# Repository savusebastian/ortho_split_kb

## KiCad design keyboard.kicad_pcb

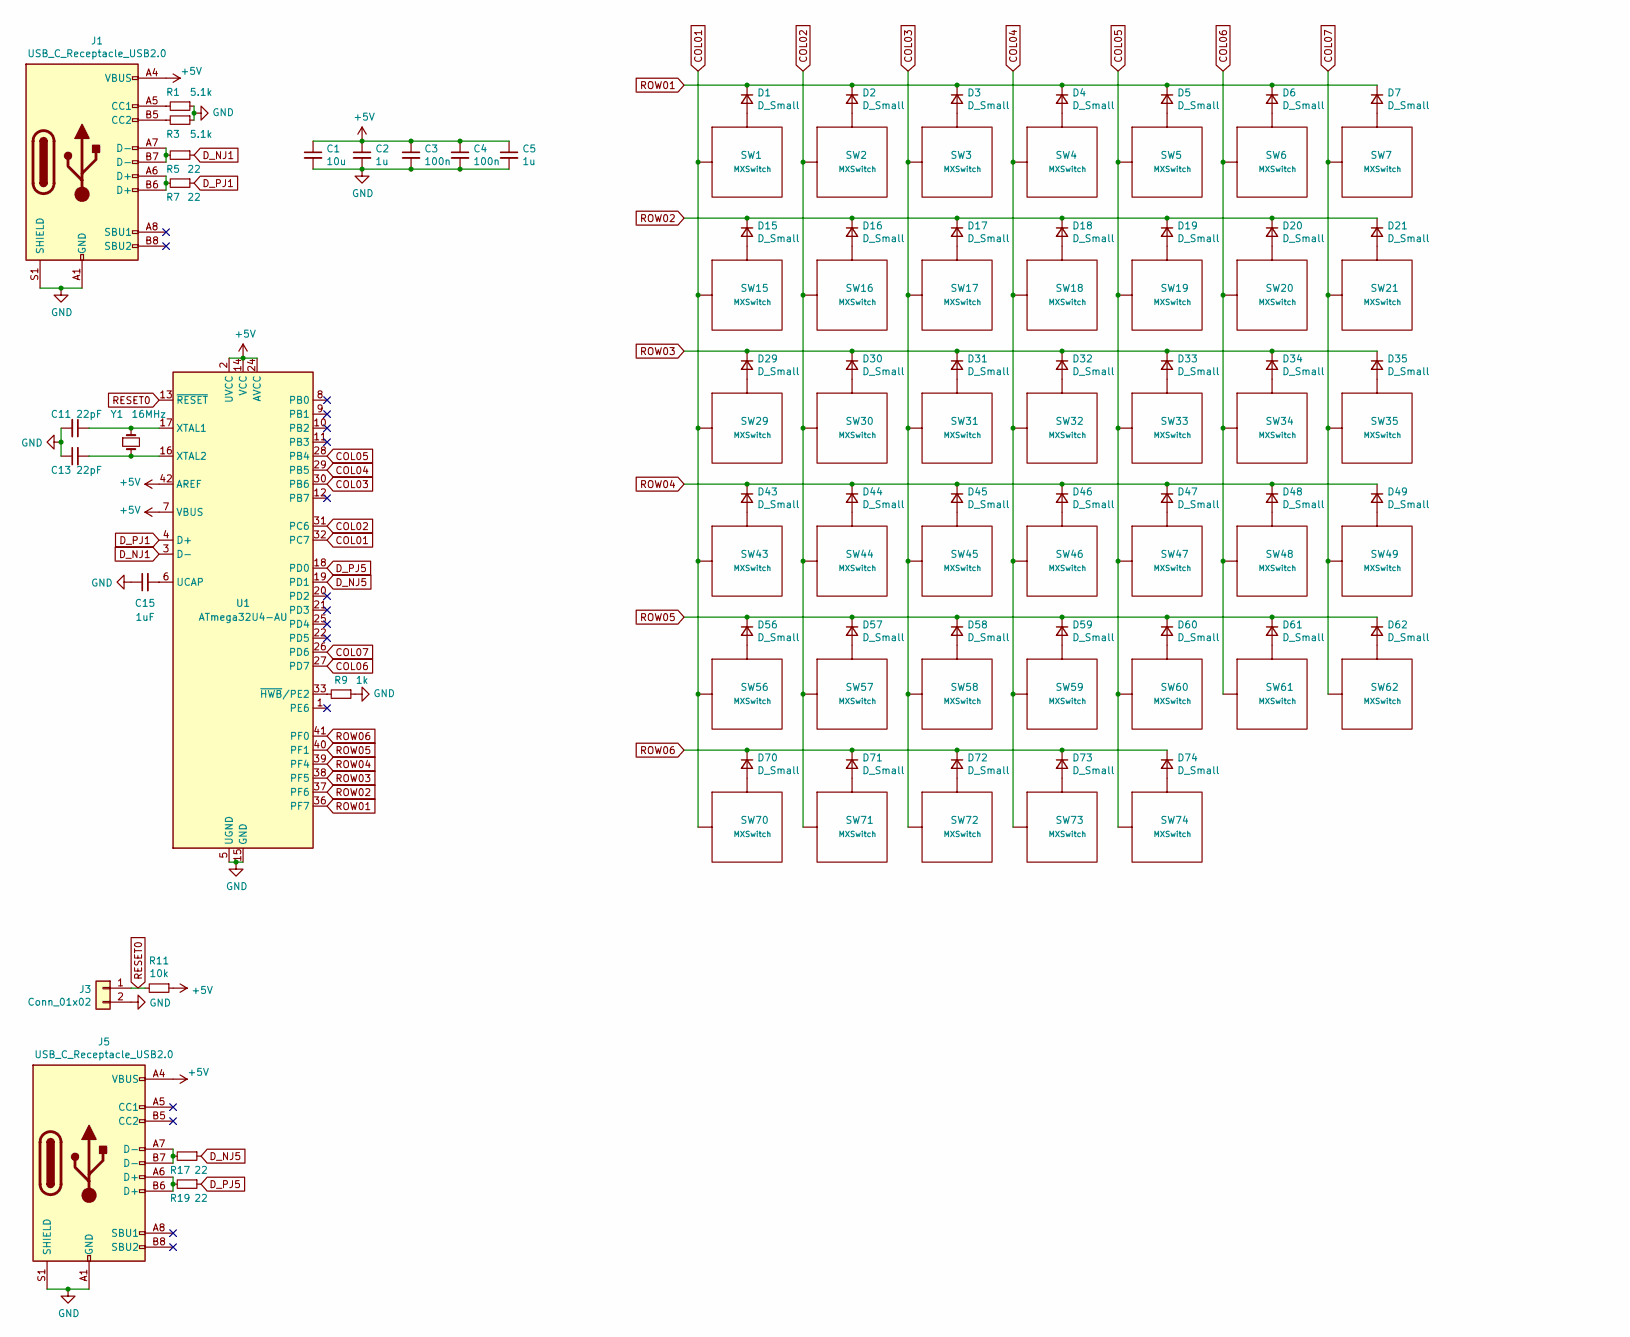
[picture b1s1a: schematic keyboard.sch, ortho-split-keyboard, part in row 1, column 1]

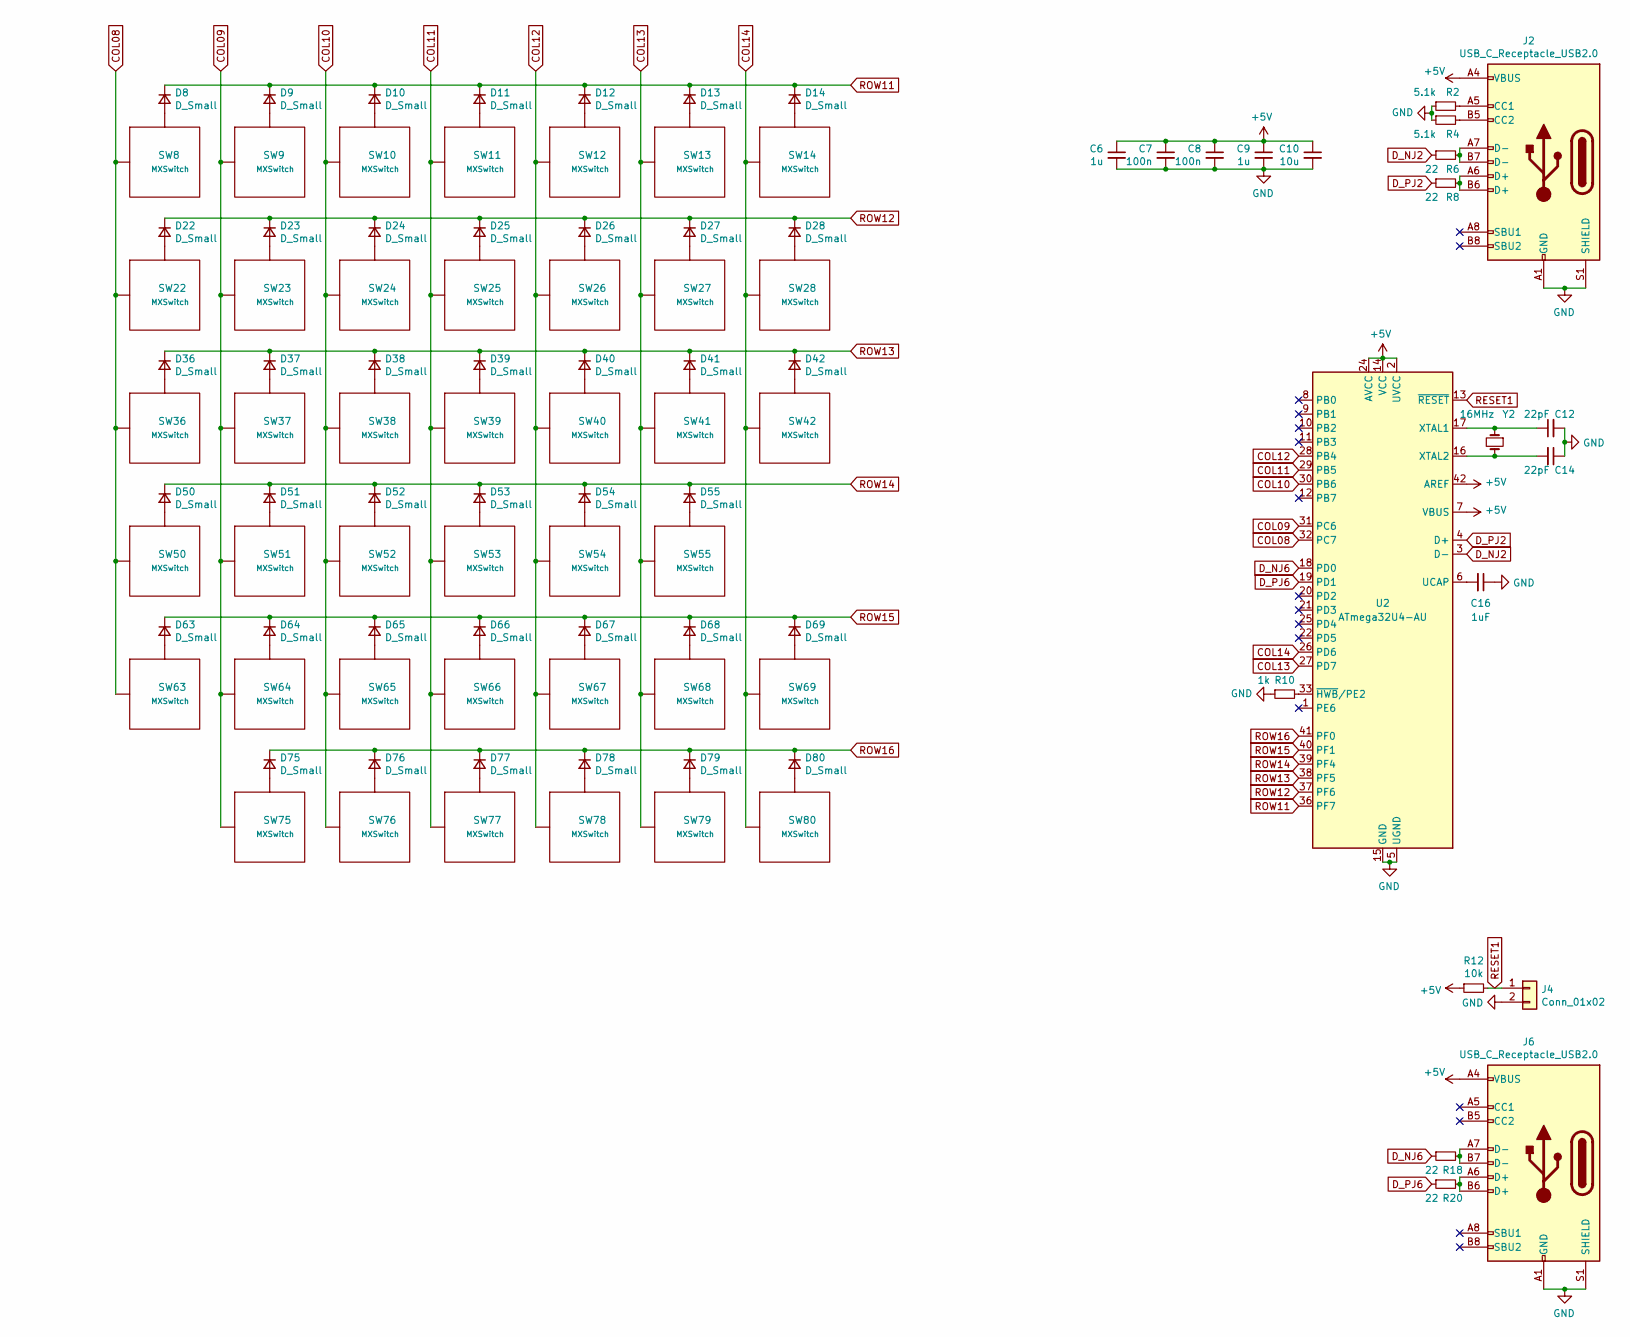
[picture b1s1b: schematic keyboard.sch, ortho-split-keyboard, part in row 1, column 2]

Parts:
C1, C10: 10u; C_0201_0603Metric; LCSC C1691
C2, C5, C6, C9: 1u; C_0201_0603Metric; LCSC C29936
C3, C4, C7, C8: 100n; C_0201_0603Metric; LCSC C1591
C11, C12, C13, C14: 22pF; C_0201_0603Metric; LCSC C1653
C15, C16: 1uF; C_0201_0603Metric; LCSC C29936
D1, D2, D3, D4, D5, D6, D7, D8, D9, D10, D11, D12, D13, D14, D15, D16, D17, D18, D19, D20, D21, D22, D23, D24, D25, D26, D27, D28, D29, D30, D31, D32, D33, D34, D35, D36, D37, D38, D39, D40, D41, D42, D43, D44, D45, D46, D47, D48, D49, D50, D51, D52, D53, D54, D55, D56, D57, D58, D59, D60, D61, D62, D63, D64, D65, D66, D67, D68, D69, D70, D71, D72, D73, D74, D75, D76, D77, D78, D79, D80: D_Small; D_0603_1608Metric; LCSC C316054
J1, J2, J5, J6: USB_C_Receptacle_USB2.0; USB_C_Receptacle_Amphenol_12401548E4-2A
J3, J4: Conn_01x02; PinHeader_1x02_P2.54mm_Vertical
R1, R2, R3, R4: 5.1k; R_0603_1608Metric; LCSC C14677
R5, R6, R7, R8, R17, R18, R19, R20: 22; R_0603_1608Metric; LCSC C108405
R9, R10: 1k; R_0603_1608Metric; LCSC C14676
R11, R12: 10k; R_0603_1608Metric; LCSC C98220
SW1, SW2, SW3, SW4, SW5, SW6, SW7, SW8, SW9, SW10, SW11, SW12, SW13, SW14, SW15, SW16, SW17, SW18, SW19, SW20, SW21, SW22, SW23, SW24, SW25, SW26, SW27, SW28, SW29, SW30, SW31, SW32, SW33, SW34, SW35, SW36, SW37, SW38, SW39, SW40, SW41, SW42, SW43, SW44, SW45, SW46, SW47, SW48, SW49, SW50, SW51, SW52, SW53, SW54, SW56, SW57, SW58, SW59, SW60, SW61, SW62, SW63, SW64, SW65, SW66, SW67, SW68, SW69, SW70, SW71, SW72, SW73, SW75, SW76, SW77, SW78, SW79, SW80: MXSwitch; SW_Cherry_MX_1.00u_PCB
SW55, SW74: MXSwitch; SW_Cherry_MX_2.00u_PCB
U1, U2: ATmega32U4-AU; TQFP-44_10x10mm_P0.8mm; LCSC C44854
Y1, Y2: 16MHz; Crystal_SMD_5032-2Pin_5.0x3.2mm; LCSC C568455

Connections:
+5V: C1.1, C2.1, C3.1, C4.1, C5.1, C6.1, C7.1, C8.1, C9.1, C10.1, J1.A4 (VBUS), J1.A9 (VBUS), J1.B4 (VBUS), J1.B9 (VBUS), J2.A4 (VBUS), J2.A9 (VBUS), J2.B4 (VBUS), J2.B9 (VBUS), J5.A4 (VBUS), J5.A9 (VBUS), J5.B4 (VBUS), J5.B9 (VBUS), J6.A4 (VBUS), J6.A9 (VBUS), J6.B4 (VBUS), J6.B9 (VBUS), R11.1, R12.1, U1.2 (UVCC), U1.7 (VBUS), U1.14 (VCC), U1.24 (AVCC), U1.34 (VCC), U1.42 (AREF), U1.44 (AVCC), U2.2 (UVCC), U2.7 (VBUS), U2.14 (VCC), U2.24 (AVCC), U2.34 (VCC), U2.42 (AREF), U2.44 (AVCC)
COL01: SW1.1 (Col), SW15.1 (Col), SW29.1 (Col), SW43.1 (Col), SW56.1 (Col), SW70.1 (Col), U1.32 (PC7)
COL02: SW2.1 (Col), SW16.1 (Col), SW30.1 (Col), SW44.1 (Col), SW57.1 (Col), SW71.1 (Col), U1.31 (PC6)
COL03: SW3.1 (Col), SW17.1 (Col), SW31.1 (Col), SW45.1 (Col), SW58.1 (Col), SW72.1 (Col), U1.30 (PB6)
COL04: SW4.1 (Col), SW18.1 (Col), SW32.1 (Col), SW46.1 (Col), SW59.1 (Col), SW73.1 (Col), U1.29 (PB5)
COL05: SW5.1 (Col), SW19.1 (Col), SW33.1 (Col), SW47.1 (Col), SW60.1 (Col), SW74.1 (Col), U1.28 (PB4)
COL06: SW6.1 (Col), SW20.1 (Col), SW34.1 (Col), SW48.1 (Col), SW61.1 (Col), U1.27 (PD7)
COL07: SW7.1 (Col), SW21.1 (Col), SW35.1 (Col), SW49.1 (Col), SW62.1 (Col), U1.26 (PD6)
COL08: SW8.1 (Col), SW22.1 (Col), SW36.1 (Col), SW50.1 (Col), SW63.1 (Col), U2.32 (PC7)
COL09: SW9.1 (Col), SW23.1 (Col), SW37.1 (Col), SW51.1 (Col), SW64.1 (Col), SW75.1 (Col), U2.31 (PC6)
COL10: SW10.1 (Col), SW24.1 (Col), SW38.1 (Col), SW52.1 (Col), SW65.1 (Col), SW76.1 (Col), U2.30 (PB6)
COL11: SW11.1 (Col), SW25.1 (Col), SW39.1 (Col), SW53.1 (Col), SW66.1 (Col), SW77.1 (Col), U2.29 (PB5)
COL12: SW12.1 (Col), SW26.1 (Col), SW40.1 (Col), SW54.1 (Col), SW67.1 (Col), SW78.1 (Col), U2.28 (PB4)
COL13: SW13.1 (Col), SW27.1 (Col), SW41.1 (Col), SW55.1 (Col), SW68.1 (Col), SW79.1 (Col), U2.27 (PD7)
COL14: SW14.1 (Col), SW28.1 (Col), SW42.1 (Col), SW69.1 (Col), SW80.1 (Col), U2.26 (PD6)
D_NJ1: R5.1, U1.3 (D-)
D_NJ2: R6.1, U2.3 (D-)
D_NJ5: R17.1, U1.19 (PD1); also elsewhere on the board
D_NJ6: R18.1, U2.18 (PD0); also elsewhere on the board
D_PJ1: R7.1, U1.4 (D+)
D_PJ2: R8.1, U2.4 (D+)
D_PJ5: R19.1, U1.18 (PD0); also elsewhere on the board
D_PJ6: R20.1, U2.19 (PD1); also elsewhere on the board
GND: C1.2, C2.2, C3.2, C4.2, C5.2, C6.2, C7.2, C8.2, C9.2, C10.2, C11.2, C12.2, C13.1, C14.1, C15.1, C16.1, J1.A1 (GND), J1.A12 (GND), J1.B1 (GND), J1.B12 (GND), J1.S1 (SHIELD), J2.A1 (GND), J2.A12 (GND), J2.B1 (GND), J2.B12 (GND), J2.S1 (SHIELD), J3.2, J4.2, J5.A1 (GND), J5.A12 (GND), J5.B1 (GND), J5.B12 (GND), J5.S1 (SHIELD), J6.A1 (GND), J6.A12 (GND), J6.B1 (GND), J6.B12 (GND), J6.S1 (SHIELD), R1.1, R2.1, R3.1, R4.1, R9.1, R10.1, U1.5 (UGND), U1.15 (GND), U1.23 (GND), U1.35 (GND), U1.43 (GND), U2.5 (UGND), U2.15 (GND), U2.23 (GND), U2.35 (GND), U2.43 (GND)
unnamed: C11.1, U1.17 (XTAL1), Y1.1
unnamed: C12.1, U2.17 (XTAL1), Y2.1
unnamed: C13.2, U1.16 (XTAL2), Y1.2
unnamed: C14.2, U2.16 (XTAL2), Y2.2
unnamed: C15.2, U1.6 (UCAP)
unnamed: C16.2, U2.6 (UCAP)
unnamed: D1.2 (A), SW1.2 (Row)
unnamed: D2.2 (A), SW2.2 (Row)
unnamed: D3.2 (A), SW3.2 (Row)
unnamed: D4.2 (A), SW4.2 (Row)
unnamed: D5.2 (A), SW5.2 (Row)
unnamed: D6.2 (A), SW6.2 (Row)
unnamed: D7.2 (A), SW7.2 (Row)
unnamed: D8.2 (A), SW8.2 (Row)
unnamed: D9.2 (A), SW9.2 (Row)
unnamed: D10.2 (A), SW10.2 (Row)
unnamed: D11.2 (A), SW11.2 (Row)
unnamed: D12.2 (A), SW12.2 (Row)
unnamed: D13.2 (A), SW13.2 (Row)
unnamed: D14.2 (A), SW14.2 (Row)
unnamed: D15.2 (A), SW15.2 (Row)
unnamed: D16.2 (A), SW16.2 (Row)
unnamed: D17.2 (A), SW17.2 (Row)
unnamed: D18.2 (A), SW18.2 (Row)
unnamed: D19.2 (A), SW19.2 (Row)
unnamed: D20.2 (A), SW20.2 (Row)
unnamed: D21.2 (A), SW21.2 (Row)
unnamed: D22.2 (A), SW22.2 (Row)
unnamed: D23.2 (A), SW23.2 (Row)
unnamed: D24.2 (A), SW24.2 (Row)
unnamed: D25.2 (A), SW25.2 (Row)
unnamed: D26.2 (A), SW26.2 (Row)
unnamed: D27.2 (A), SW27.2 (Row)
unnamed: D28.2 (A), SW28.2 (Row)
unnamed: D29.2 (A), SW29.2 (Row)
unnamed: D30.2 (A), SW30.2 (Row)
unnamed: D31.2 (A), SW31.2 (Row)
unnamed: D32.2 (A), SW32.2 (Row)
unnamed: D33.2 (A), SW33.2 (Row)
unnamed: D34.2 (A), SW34.2 (Row)
unnamed: D35.2 (A), SW35.2 (Row)
unnamed: D36.2 (A), SW36.2 (Row)
unnamed: D37.2 (A), SW37.2 (Row)
unnamed: D38.2 (A), SW38.2 (Row)
unnamed: D39.2 (A), SW39.2 (Row)
unnamed: D40.2 (A), SW40.2 (Row)
unnamed: D41.2 (A), SW41.2 (Row)
unnamed: D42.2 (A), SW42.2 (Row)
unnamed: D43.2 (A), SW43.2 (Row)
unnamed: D44.2 (A), SW44.2 (Row)
unnamed: D45.2 (A), SW45.2 (Row)
unnamed: D46.2 (A), SW46.2 (Row)
unnamed: D47.2 (A), SW47.2 (Row)
unnamed: D48.2 (A), SW48.2 (Row)
unnamed: D49.2 (A), SW49.2 (Row)
unnamed: D50.2 (A), SW50.2 (Row)
unnamed: D51.2 (A), SW51.2 (Row)
unnamed: D52.2 (A), SW52.2 (Row)
unnamed: D53.2 (A), SW53.2 (Row)
unnamed: D54.2 (A), SW54.2 (Row)
unnamed: D55.2 (A), SW55.2 (Row)
unnamed: D56.2 (A), SW56.2 (Row)
unnamed: D57.2 (A), SW57.2 (Row)
unnamed: D58.2 (A), SW58.2 (Row)
unnamed: D59.2 (A), SW59.2 (Row)
unnamed: D60.2 (A), SW60.2 (Row)
unnamed: D61.2 (A), SW61.2 (Row)
unnamed: D62.2 (A), SW62.2 (Row)
unnamed: D63.2 (A), SW63.2 (Row)
unnamed: D64.2 (A), SW64.2 (Row)
unnamed: D65.2 (A), SW65.2 (Row)
unnamed: D66.2 (A), SW66.2 (Row)
unnamed: D67.2 (A), SW67.2 (Row)
unnamed: D68.2 (A), SW68.2 (Row)
unnamed: D69.2 (A), SW69.2 (Row)
unnamed: D70.2 (A), SW70.2 (Row)
unnamed: D71.2 (A), SW71.2 (Row)
unnamed: D72.2 (A), SW72.2 (Row)
unnamed: D73.2 (A), SW73.2 (Row)
unnamed: D74.2 (A), SW74.2 (Row)
unnamed: D75.2 (A), SW75.2 (Row)
unnamed: D76.2 (A), SW76.2 (Row)
unnamed: D77.2 (A), SW77.2 (Row)
unnamed: D78.2 (A), SW78.2 (Row)
unnamed: D79.2 (A), SW79.2 (Row)
unnamed: D80.2 (A), SW80.2 (Row)
unnamed: J1.A5 (CC1), R1.2
unnamed: J1.A6 (D+), J1.B6 (D+), R7.2
unnamed: J1.A7 (D-), J1.B7 (D-), R5.2
unnamed: J1.B5 (CC2), R3.2
unnamed: J2.A5 (CC1), R2.2
unnamed: J2.A6 (D+), J2.B6 (D+), R8.2
unnamed: J2.A7 (D-), J2.B7 (D-), R6.2
unnamed: J2.B5 (CC2), R4.2
unnamed 123: J5.A6 (D+), J5.B6 (D+), R19.2; also elsewhere on the board
unnamed 124: J5.A7 (D-), J5.B7 (D-), R17.2; also elsewhere on the board
unnamed 129: J6.A6 (D+), J6.B6 (D+), R20.2; also elsewhere on the board
unnamed 130: J6.A7 (D-), J6.B7 (D-), R18.2; also elsewhere on the board
unnamed: R9.2, U1.33 (~HWB~/PE2)
unnamed: R10.2, U2.33 (~HWB~/PE2)
RESET0: J3.1, R11.2, U1.13 (~RESET)
RESET1: J4.1, R12.2, U2.13 (~RESET)
ROW01: D1.1 (K), D2.1 (K), D3.1 (K), D4.1 (K), D5.1 (K), D6.1 (K), D7.1 (K), U1.36 (PF7)
ROW02: D15.1 (K), D16.1 (K), D17.1 (K), D18.1 (K), D19.1 (K), D20.1 (K), D21.1 (K), U1.37 (PF6)
ROW03: D29.1 (K), D30.1 (K), D31.1 (K), D32.1 (K), D33.1 (K), D34.1 (K), D35.1 (K), U1.38 (PF5)
ROW04: D43.1 (K), D44.1 (K), D45.1 (K), D46.1 (K), D47.1 (K), D48.1 (K), D49.1 (K), U1.39 (PF4)
ROW05: D56.1 (K), D57.1 (K), D58.1 (K), D59.1 (K), D60.1 (K), D61.1 (K), D62.1 (K), U1.40 (PF1)
ROW06: D70.1 (K), D71.1 (K), D72.1 (K), D73.1 (K), D74.1 (K), U1.41 (PF0)
ROW11: D8.1 (K), D9.1 (K), D10.1 (K), D11.1 (K), D12.1 (K), D13.1 (K), D14.1 (K), U2.36 (PF7)
ROW12: D22.1 (K), D23.1 (K), D24.1 (K), D25.1 (K), D26.1 (K), D27.1 (K), D28.1 (K), U2.37 (PF6)
ROW13: D36.1 (K), D37.1 (K), D38.1 (K), D39.1 (K), D40.1 (K), D41.1 (K), D42.1 (K), U2.38 (PF5)
ROW14: D50.1 (K), D51.1 (K), D52.1 (K), D53.1 (K), D54.1 (K), D55.1 (K), U2.39 (PF4)
ROW15: D63.1 (K), D64.1 (K), D65.1 (K), D66.1 (K), D67.1 (K), D68.1 (K), D69.1 (K), U2.40 (PF1)
ROW16: D75.1 (K), D76.1 (K), D77.1 (K), D78.1 (K), D79.1 (K), D80.1 (K), U2.41 (PF0)

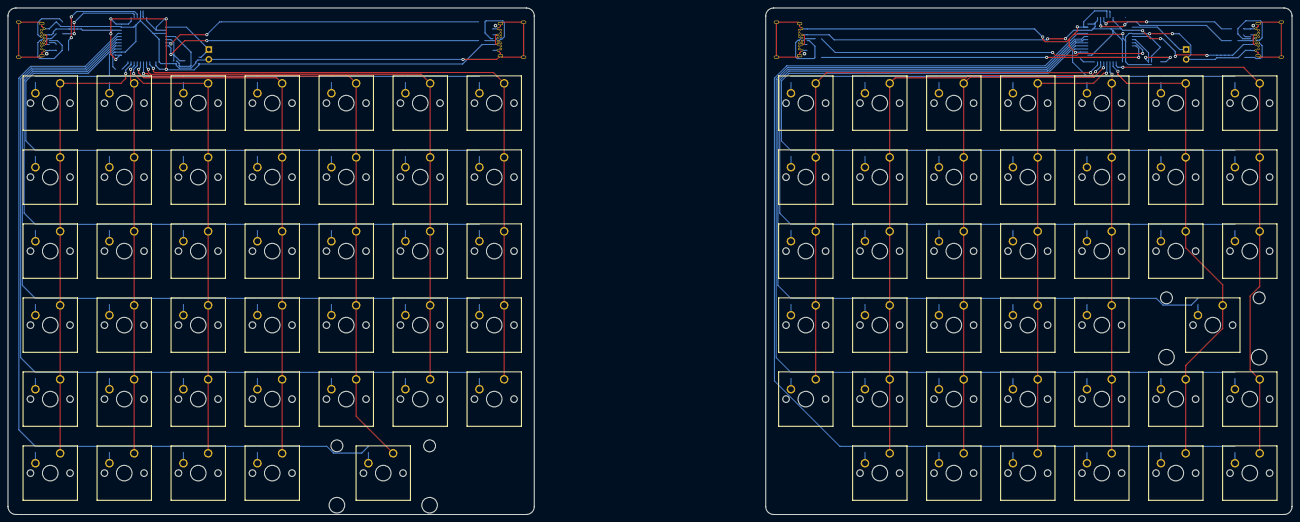
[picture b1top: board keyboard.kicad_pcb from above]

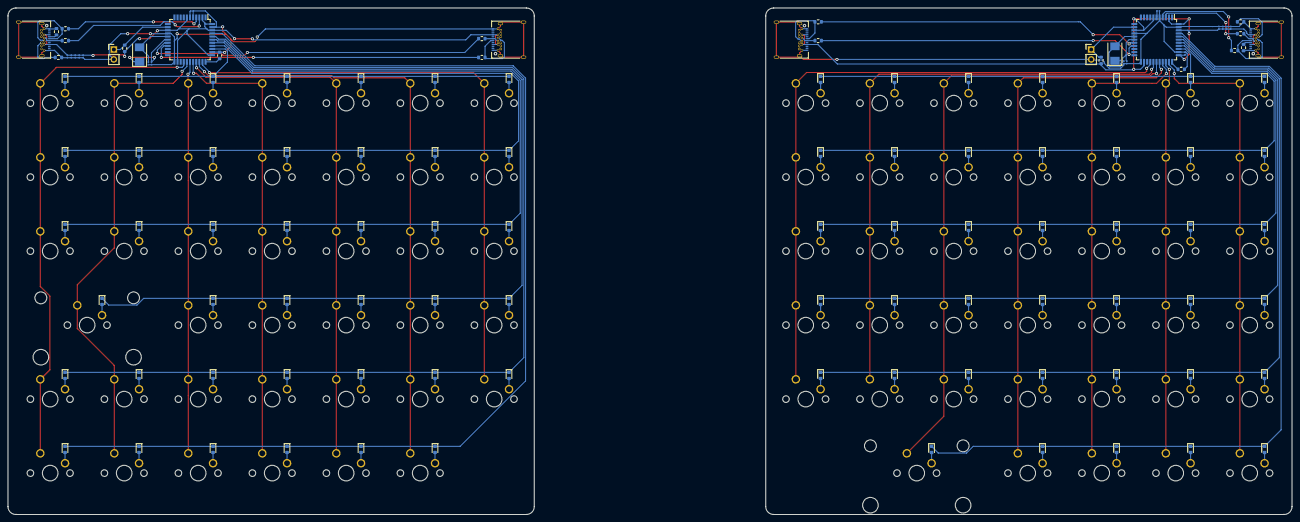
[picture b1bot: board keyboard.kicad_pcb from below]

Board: 2 copper layers, 329.7 x 130.0 mm, 202 parts (122 on the bottom side), 138 nets.

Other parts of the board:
R13, R14, R15, R16: 22; R_0603_1608Metric

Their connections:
D_NJ5: R13.1; also elsewhere on the board
D_NJ6: R14.1; also elsewhere on the board
D_PJ5: R15.1; also elsewhere on the board
D_PJ6: R16.1; also elsewhere on the board
unnamed 123: R15.2; also elsewhere on the board
unnamed 124: R13.2; also elsewhere on the board
unnamed 129: R16.2; also elsewhere on the board
unnamed 130: R14.2; also elsewhere on the board

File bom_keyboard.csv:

Comment,Designator,Footprint,LCSC Part Number
22R,"R5,R6,R7,R8,R13,R14,R15,R16",0603,C108405
1k,"R9,R10",0603,C14676
5K1,"R1,R2,R3,R4",0603,C14677
10k,"R11,R12",0603,C98220
22pF,"C11,C12,C13,C14",0603,C1653
100nF,"C3,C4,C7,C8",0603,C1591
1uF,"C2,C5,C6,C9,C15,C16",0603,C29936
10uF,"C1,C10",0603,C1691
Diodes,"D1,D2,D3,D4,D5,D6,D7,D8,D9,D10,D11,D12,D13,D14,D15,D16,D17,D18,D19,D20,D21,D22,D23,D24,D25,D26,D27,D28,D29,D30,D31,D32,D33,D34,D35,D36,D37,D38,D39,D40,D41,D42,D43,D44,D45,D46,D47,D48,D49,D50,D51,D52,D53,D54,D55,D56,D57,D58,D59,D60,D61,D62,D63,D64,D65,D66,D67,D68,D69,D70,D71,D72,D73,D74,D75,D76,D77,D78,D79,D80",0603,C316054
USB_C_Receptacle_USB2.0,"J1,J2,J5,J6",SMD,C319152
Conn_01x02,"J3,J4","Through Hole,P=2.54mm",C492401
Crystal,"Y1,Y2",SMD,C568455
ATmega32U4-AU,"U1,U2",QFP-44_10x10x08P,C44854

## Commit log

2021-07-31 Update schematics
2021-08-01 Update schematics and connect pcb
2021-08-02 Update sch and added qmk files
